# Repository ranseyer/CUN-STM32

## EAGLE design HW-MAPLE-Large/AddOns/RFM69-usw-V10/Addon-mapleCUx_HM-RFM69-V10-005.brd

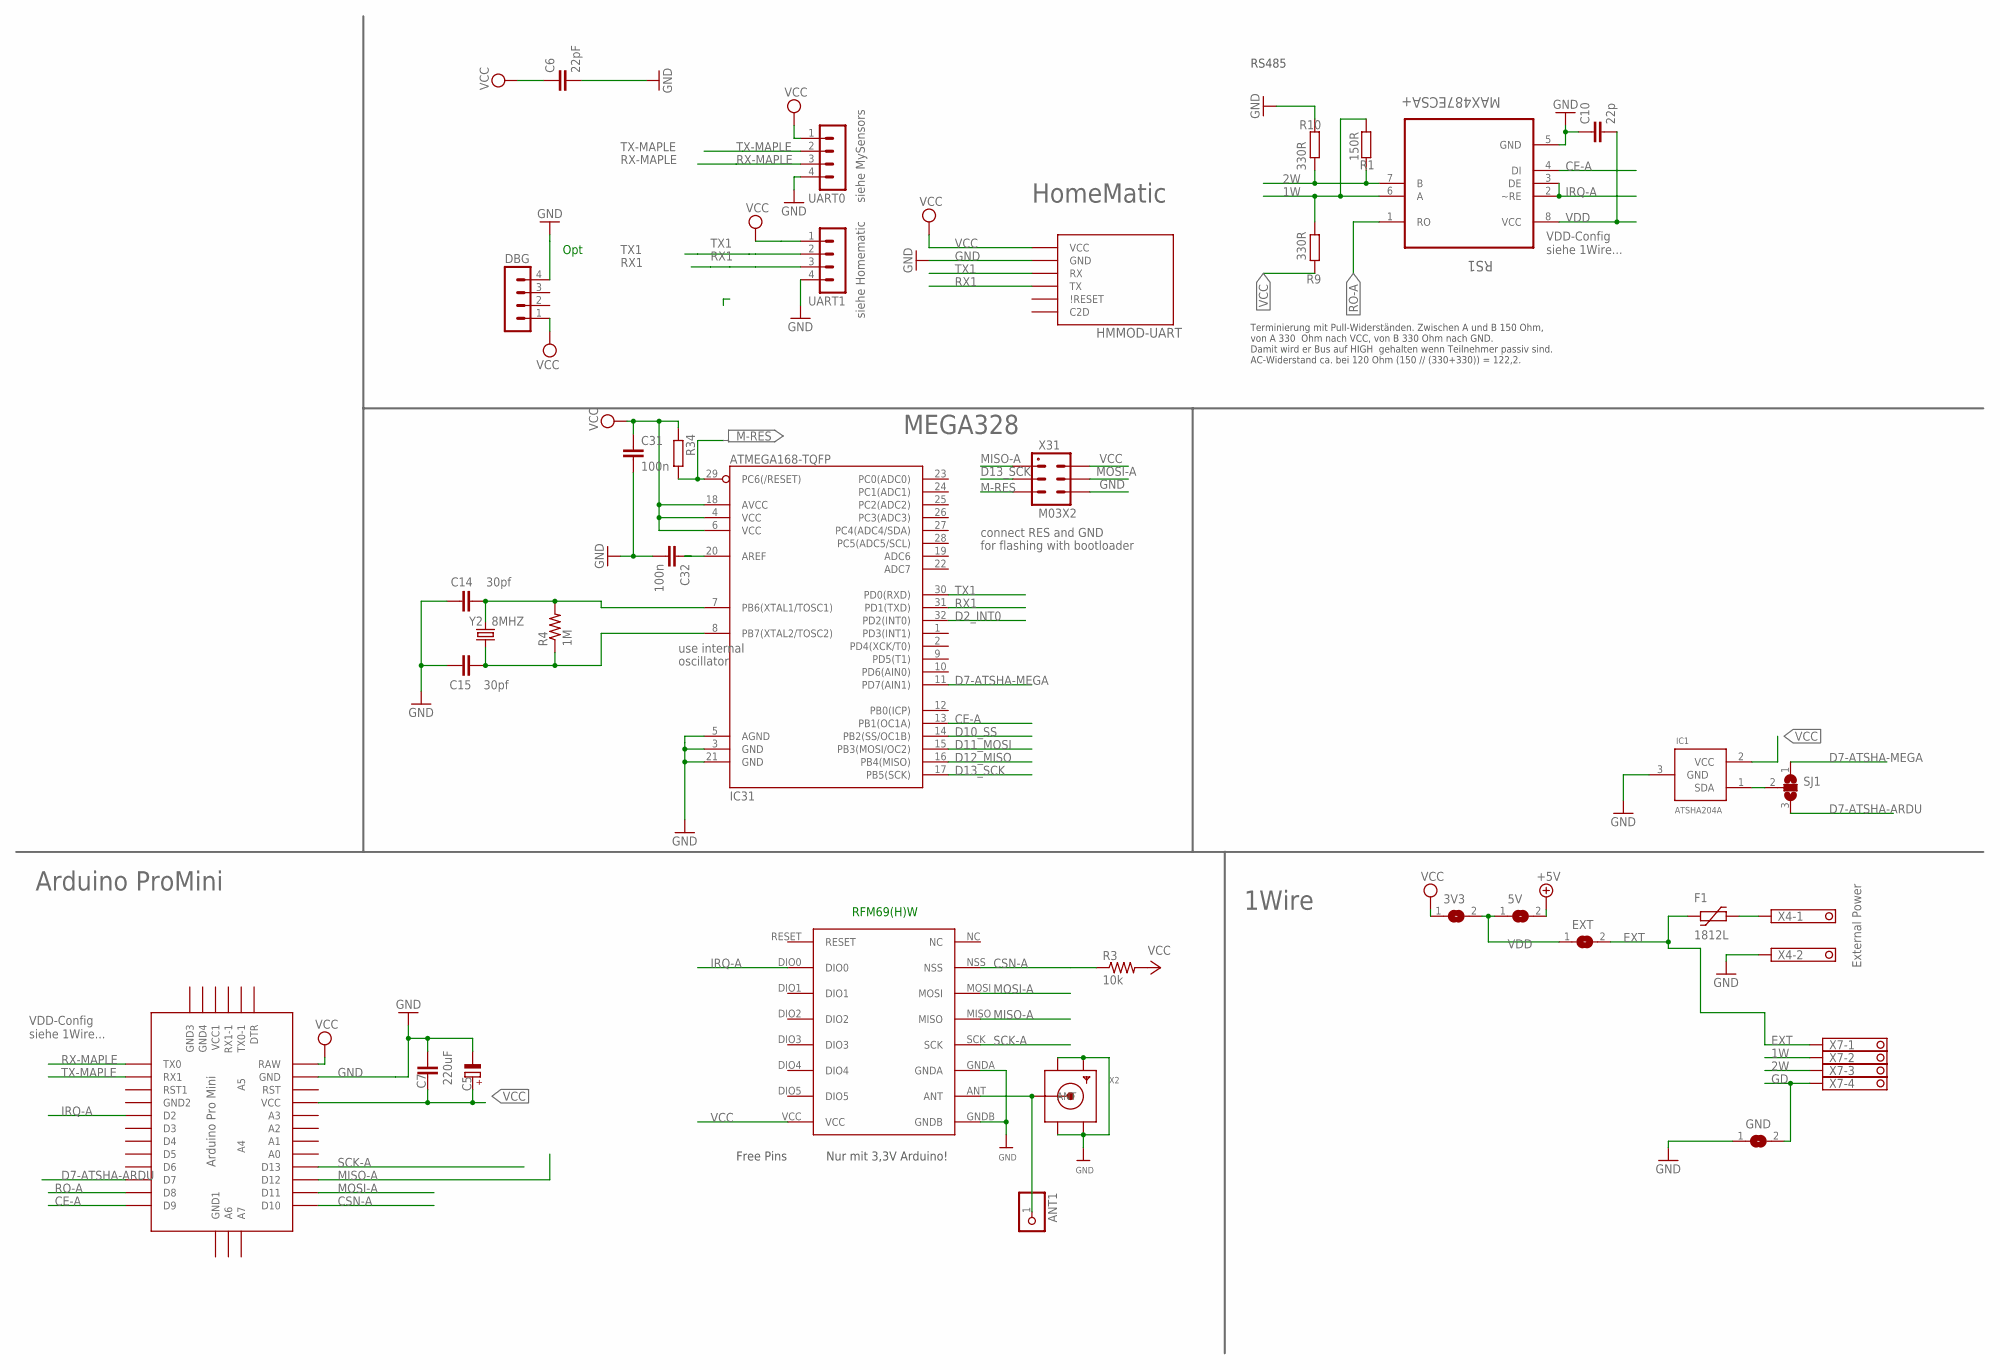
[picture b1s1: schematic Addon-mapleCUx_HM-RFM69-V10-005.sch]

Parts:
3V3, 5V: SJ
ANT1: PINHD-1X1; 1X01
C5: 220uF; E5-8,5
C6: 22pF; C0805
C7: C-EUC1812; C1812
C10: 22p; C0805
C14, C15: 30pf; 0805
C31, C32: 100n; C0805
DBG: MA04-1
EXT: SJ
F1: 1812L
GND: SJ
HMMOD-UART: HM-MOD-UARTDIL; HM-MOD-UART-DIL
IC1: ATSHA204A; SOT23
IC31: ATMEGA168-TQFP; TQFP32-08
R1: 150R; R0805
R3: 10k; 0805
R4: 1M; 0805
R9, R10: 330R; R0805
R34: R-EU_R0805; R0805
RFM69W: RFM69HW; RFM
RS1: MAX487ECSA+; SOIC127P600X175-8N
SJ1: SJ2W; SJ_2
U$2: ABK-PRO-MINI
UART0, UART1: MA04-1
X2: SMACONNECTOR_EDGE; SMA_EDGELAUNCH
X4: 1751248
X7: 1751264
X31: M03X2; 2X03-1.27MM_SMD
Y2: 8MHZ; CRYSTAL-TXC-7A

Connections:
1W: R1.1, R9.2, RS1.6 (A), X7.2
2W: R1.2, R10.1, RS1.7 (B), X7.3
+5V: 5V.2
CE-A: IC31.13 (PB1(OC1A)), RS1.4 (DI), U$2.D9
CSN-A: R3.1, RFM69W.NSS, U$2.D10
D2_INT0: IC31.32 (PD2(INT0))
D7-ATSHA-ARDU: SJ1.3, U$2.D7
D7-ATSHA-MEGA: IC31.11 (PD7(AIN1)), SJ1.1
D10_SS: IC31.14 (PB2(SS/OC1B))
D11_MOSI: IC31.15 (PB3(MOSI/OC2))
D12_MISO: IC31.16 (PB4(MISO))
D13_SCK: IC31.17 (PB5(SCK)), X31.P$3 (3)
EXT: EXT.2, F1.P$1 (1), X7.1
GD: GND.2, X7.4
GND: C5.-, C6.2, C7.1, C10.1, C14.1, C15.1, C31.2, C32.2, DBG.4, GND.1, HMMOD-UART.2 (GND), IC1.3 (GND), IC31.3 (GND), IC31.5 (AGND), IC31.21 (GND), R10.2, RFM69W.GNDA, RFM69W.GNDB, RS1.5 (GND), U$2.GND, UART0.4, UART1.4, X2.GND@1 (GND4), X2.GND@2 (GND3), X2.GND@3 (GND2), X2.GND@4 (GND1), X4.2, X31.P$6 (6)
IRQ-A: RFM69W.DIO0, RS1.2 (~RE), RS1.3 (DE), U$2.D2
M-RES: IC31.29 (PC6(/RESET)), R34.2, X31.P$5 (5)
MISO-A: RFM69W.MISO, U$2.D12, X31.P$1 (1)
MOSI-A: RFM69W.MOSI, U$2.D11, X31.P$4 (4)
unnamed: ANT1.1, RFM69W.ANT, X2.P (ANT)
unnamed: C14.2, IC31.7 (PB6(XTAL1/TOSC1)), R4.2, Y2.P$2 (2)
unnamed: IC1.1 (SDA), SJ1.2
unnamed: C32.1, IC31.20 (AREF)
unnamed: C15.2, IC31.8 (PB7(XTAL2/TOSC2)), R4.1, Y2.P$1 (1)
unnamed: F1.P$2 (2), X4.1
RO-A: RS1.1 (RO), U$2.D8
RX1: HMMOD-UART.5 (TX), IC31.31 (PD1(TXD)), UART1.3
RX-MAPLE: U$2.TX0, UART0.3
SCK-A: RFM69W.SCK, U$2.D13
TX1: HMMOD-UART.6 (RX), IC31.30 (PD0(RXD)), UART1.2
TX-MAPLE: U$2.RX1, UART0.2
VCC: 3V3.1, C5.+, C6.1, C7.2, C31.1, DBG.1, HMMOD-UART.1 (VCC), IC1.2 (VCC), IC31.4 (VCC), IC31.6 (VCC), IC31.18 (AVCC), R3.2, R9.1, R34.1, RFM69W.VCC, U$2.RAW, U$2.VCC, UART0.1, UART1.1, X31.P$2 (2)
VDD: 3V3.2, 5V.1, C10.2, EXT.1, RS1.8 (VCC)

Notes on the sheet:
Opt
siehe Homematic
siehe MySensors
HomeMatic
Arduino ProMini
MEGA328
VDD-Config siehe 1Wire...
use internal
oscillator
connect RES and GND
for flashing with bootloader
RS485
Terminierung mit Pull-Widerständen. Zwischen A und B 150 Ohm, von A 330 Ohm nach VCC, von B 330 Ohm nach GND. Damit wird er Bus auf HIGH gehalten wenn Teilnehmer passiv sind. AC-Widerstand ca. bei 120 Ohm (150 // (330+330)) = 122,2.
1Wire
External Power
Free Pins
RFM69(H)W
Nur mit 3,3V Arduino!

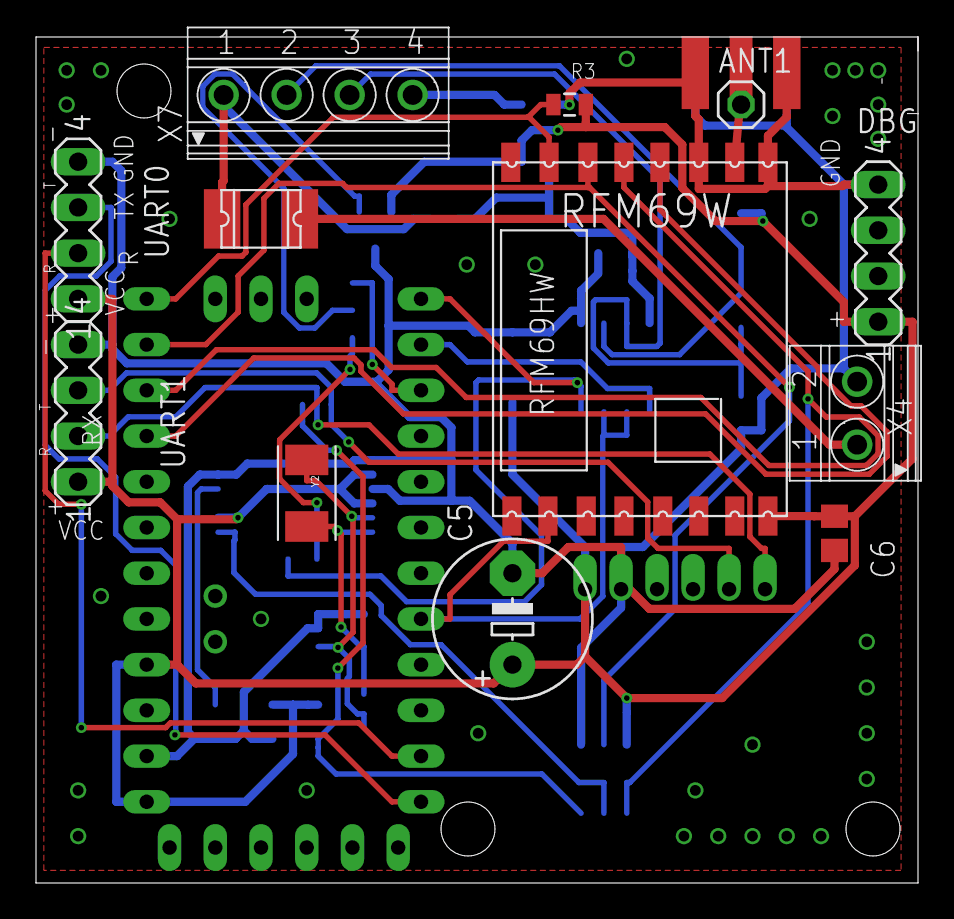
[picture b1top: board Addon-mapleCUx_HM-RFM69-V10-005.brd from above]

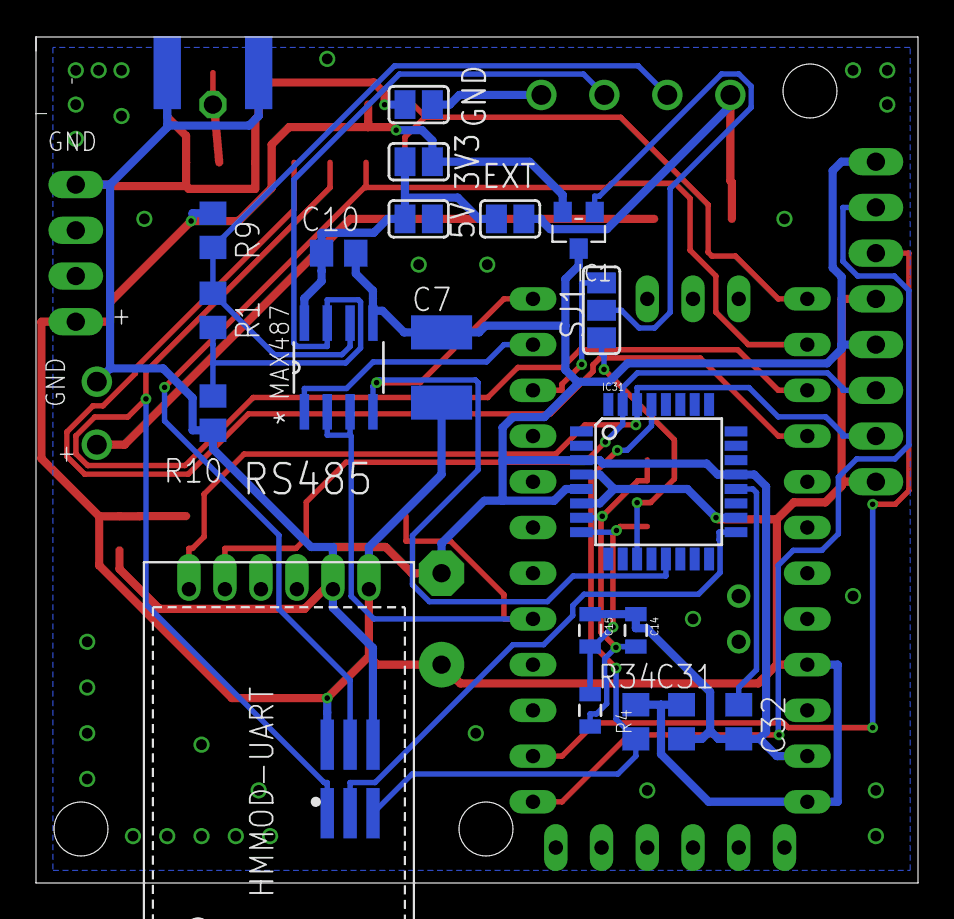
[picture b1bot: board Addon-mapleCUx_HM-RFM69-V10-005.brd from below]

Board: 2 copper layers, 49.0 x 47.0 mm, 35 parts (21 on the bottom side), 28 nets.

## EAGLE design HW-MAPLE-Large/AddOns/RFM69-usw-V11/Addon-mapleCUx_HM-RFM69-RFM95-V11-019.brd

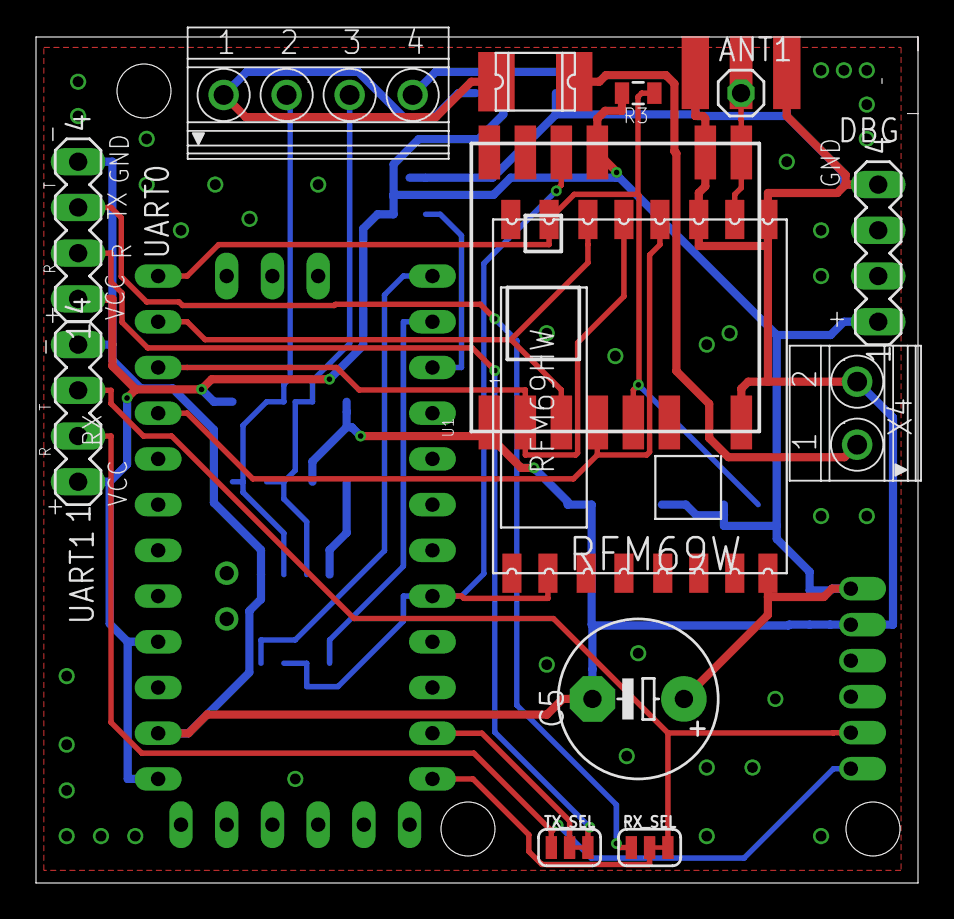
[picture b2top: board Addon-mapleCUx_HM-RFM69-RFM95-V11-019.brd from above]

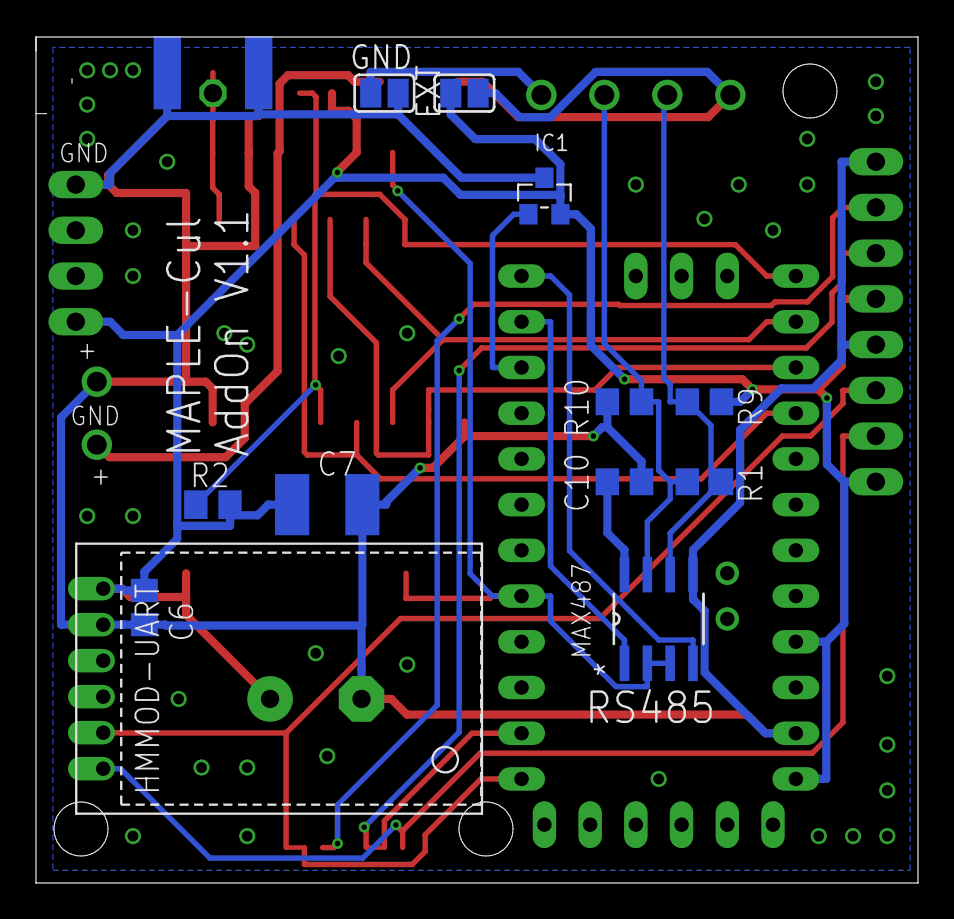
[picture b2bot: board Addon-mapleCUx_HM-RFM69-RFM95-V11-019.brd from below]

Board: 2 copper layers, 49.0 x 47.0 mm, 27 parts (12 on the bottom side), 23 nets.

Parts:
ANT1: 1X01
C5: 220uF; E5-8,5
C6: 22pF; C0805
C7: C1812
C10: 22p; C0805
DBG: MA04-1
EXT: SJ
F1: 1812L
GND: SJ
HMMOD-UART: HM-MOD-UARTDIL; HM-MOD-UART-DIL
IC1: ATSHA204A; SOT23
R1: 150R; R0805
R2: 10k; M0805
R3: 10k; 0805
R9, R10: 330R; R0805
RFM69W: RFM69HW; RFM
RS1: MAX487ECSA+; SOIC127P600X175-8N
RX_SEL: JUMPER-SMT_3_1-NC_TRACE_SILK; SMT-JUMPER_3_1-NC_TRACE_SILK
TX_SEL: JUMPER-SMT_3_1-NC_TRACE_SILK; SMT-JUMPER_3_1-NC_TRACE_SILK
U1: RFM69HCW; RFM69HCW-XXXS2
U$2: ABK-PRO-MINI
UART0, UART1: MA04-1
X2: SMA_EDGELAUNCH
X4: 1751248
X7: 1751264

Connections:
1W: R1.1, R9.2, RS1.6, X7.2
2W: R1.2, R10.1, RS1.7, X7.3
ANT: ANT1.1, RFM69W.ANT, U1.ANT, X2.P
CE-A: RS1.4, U$2.D9
CSN-A: R2.1, R3.1, RFM69W.NSS, U1.NSS, U$2.D10
D7-ATSHA-ARDU: IC1.1, U$2.D7
EXT: EXT.2, F1.P$1, X7.1
GD: GND.2, X7.4
GND: C5.-, C6.2, C7.1, C10.1, DBG.4, GND.1, HMMOD-UART.2, IC1.3, R10.2, RFM69W.GNDA, RFM69W.GNDB, RS1.5, U1.GND_1, U1.GND_2, U1.GND_3, U$2.GND, UART0.4, UART1.4, X2.GND@1, X2.GND@2, X2.GND@3, X2.GND@4, X4.2
IRQ-A: RFM69W.DIO0, RS1.2, RS1.3, U1.DIO0, U$2.D2
MISO-A: RFM69W.MISO, U1.MISO, U$2.D12
MOSI-A: RFM69W.MOSI, U1.MOSI, U$2.D11
unnamed: F1.P$2, X4.1
RO-A: RS1.1, U$2.D8
RX: TX_SEL.2, U$2.RX1
RX0: RX_SEL.1, UART0.3
RX1: HMMOD-UART.5, RX_SEL.3, UART1.3
SCK-A: RFM69W.SCK, U1.SCK, U$2.D13
TX: RX_SEL.2, U$2.TX0
TX0: TX_SEL.3, UART0.2
TX1: HMMOD-UART.6, TX_SEL.1, UART1.2
VCC: C5.+, C6.1, C7.2, DBG.1, EXT.1, HMMOD-UART.1, IC1.2, R2.2, R3.2, R9.1, RFM69W.VCC, U1.3.3V, U$2.RAW, U$2.VCC, UART0.1, UART1.1
VDD: C10.2, RS1.8

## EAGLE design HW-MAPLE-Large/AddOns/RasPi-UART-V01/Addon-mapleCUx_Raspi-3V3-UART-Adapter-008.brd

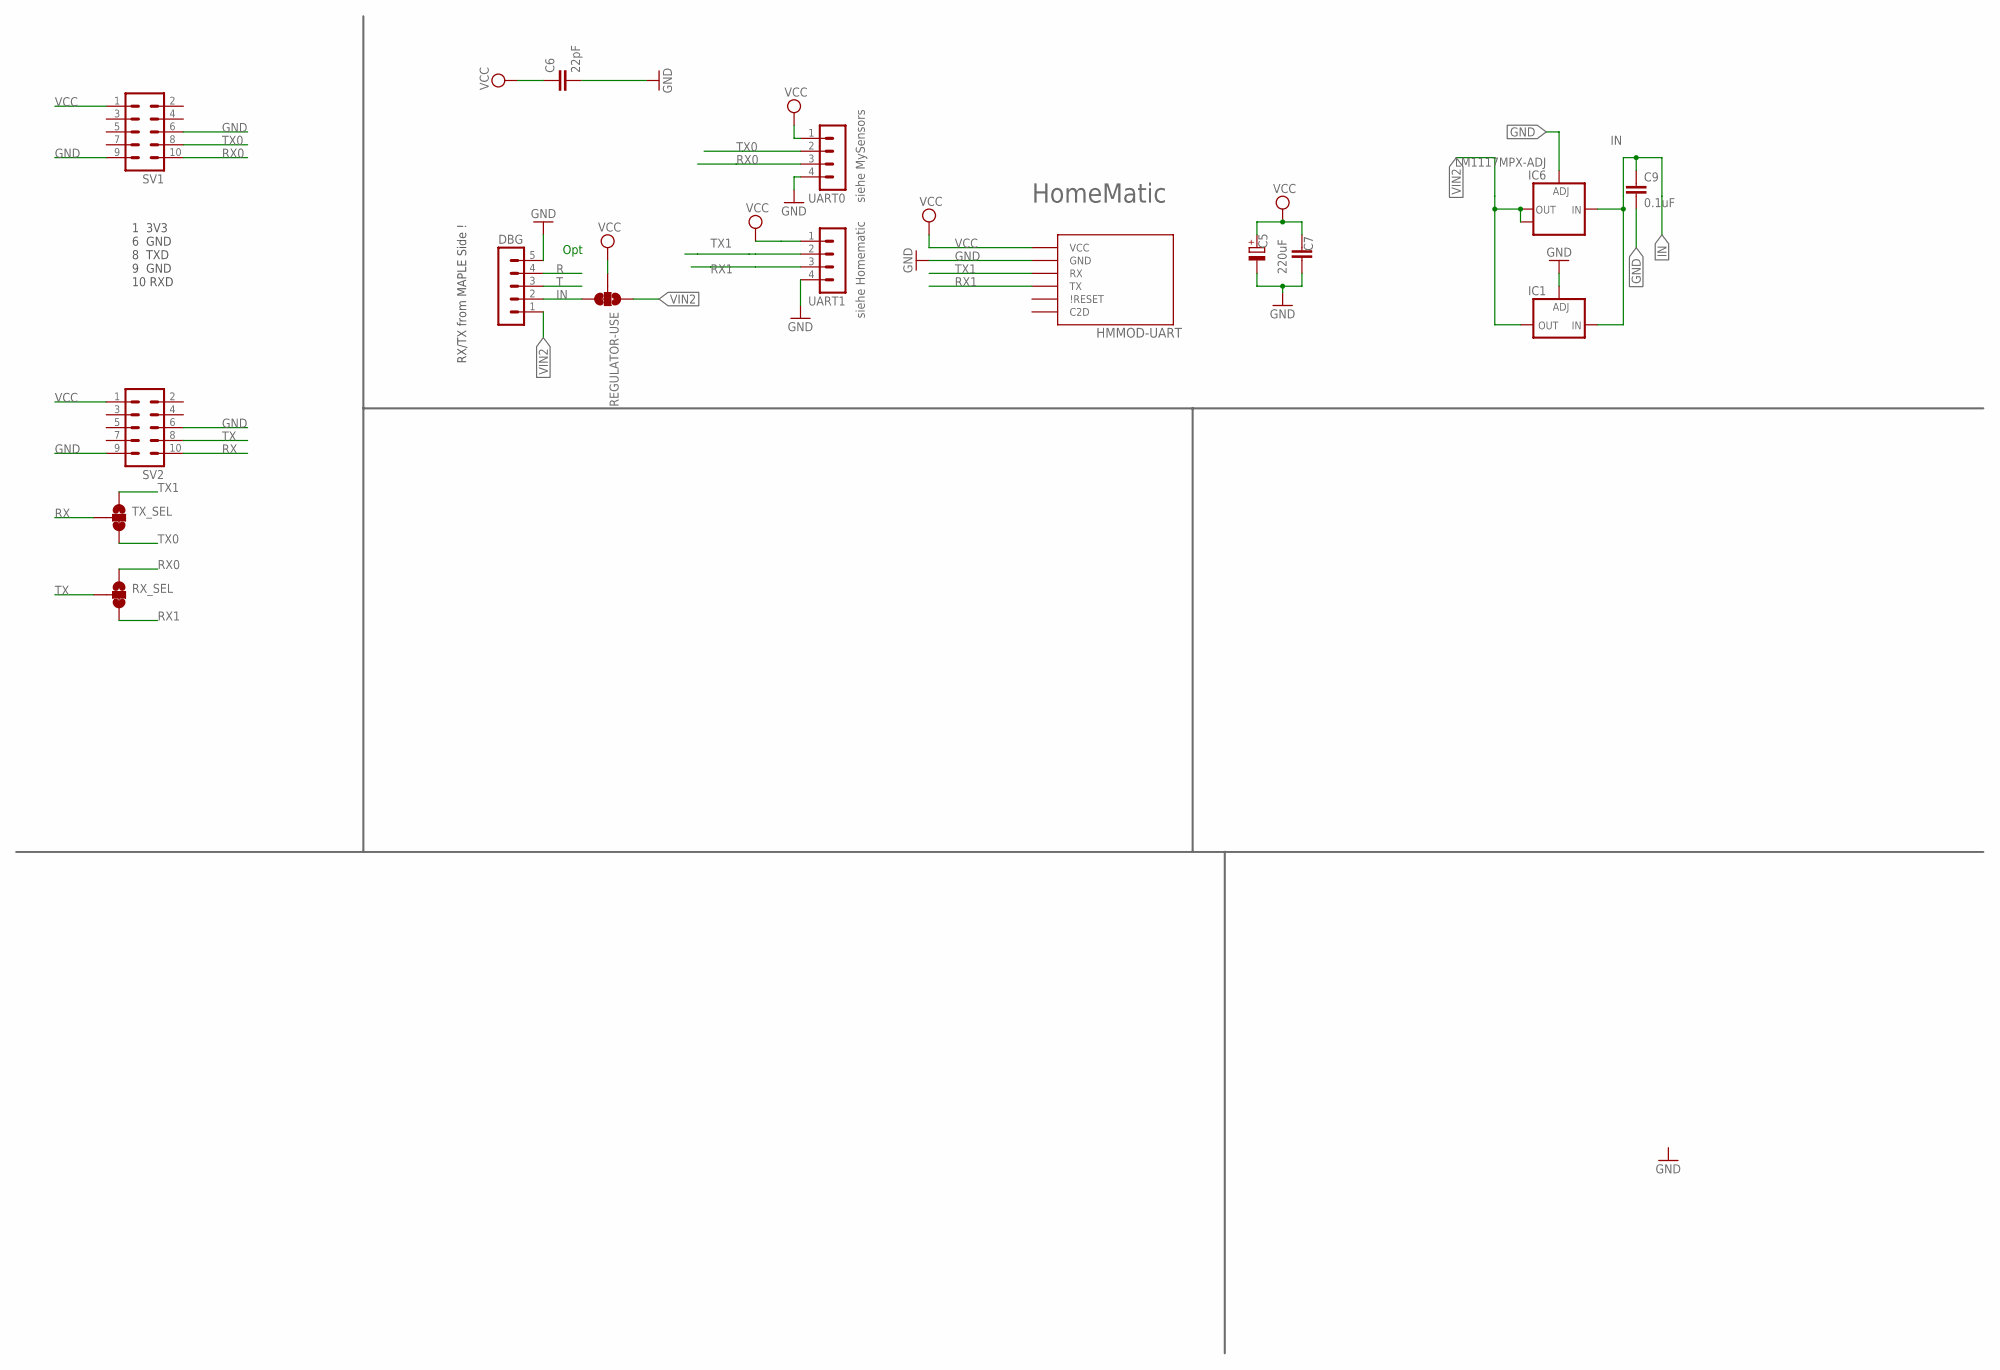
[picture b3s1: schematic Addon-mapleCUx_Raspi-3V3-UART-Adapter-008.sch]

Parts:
C5: 220uF; E5-8,5
C6: 22pF; C0805
C7: C-EUC1812; C1812
C9: 0.1uF; C1206
DBG: MA05-1
HMMOD-UART: HM-MOD-UARTDIL; HM-MOD-UART-DIL
IC1: LD117ADT50TR; DPACK
IC6: LM1117MPX-ADJ; SOT223
REGULATOR-USE: JUMPER-SMT_3_1-NC_TRACE_SILK; SMT-JUMPER_3_1-NC_TRACE_SILK
RX_SEL: JUMPER-SMT_3_1-NC_TRACE_SILK; SMT-JUMPER_3_1-NC_TRACE_SILK
SV1, SV2: MA05-2
TX_SEL: JUMPER-SMT_3_1-NC_TRACE_SILK; SMT-JUMPER_3_1-NC_TRACE_SILK
UART0, UART1: MA04-1

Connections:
GND: C5.-, C6.2, C7.1, C9.2, DBG.5, HMMOD-UART.2 (GND), IC1.1 (ADJ), IC6.1 (ADJ), SV1.6, SV1.9, SV2.6, SV2.9, UART0.4, UART1.4
IN: C9.1, DBG.2, IC1.3 (IN), IC6.3 (IN), REGULATOR-USE.3
R: DBG.4
RX: SV2.10, TX_SEL.2
RX0: RX_SEL.1, SV1.10, UART0.3
RX1: HMMOD-UART.5 (TX), RX_SEL.3, UART1.3
T: DBG.3
TX: RX_SEL.2, SV2.8
TX0: SV1.8, TX_SEL.3, UART0.2
TX1: HMMOD-UART.6 (RX), TX_SEL.1, UART1.2
VCC: C5.+, C6.1, C7.2, HMMOD-UART.1 (VCC), REGULATOR-USE.2, SV1.1, SV2.1, UART0.1, UART1.1
VIN2: DBG.1, IC1.4 (OUT), IC6.2 (OUT), IC6.TAB (OUT1), REGULATOR-USE.1

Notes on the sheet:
Opt
siehe Homematic
siehe MySensors
HomeMatic
1 3V3 6 GND 8 TXD 9 GND 10 RXD
RX/TX from MAPLE Side !

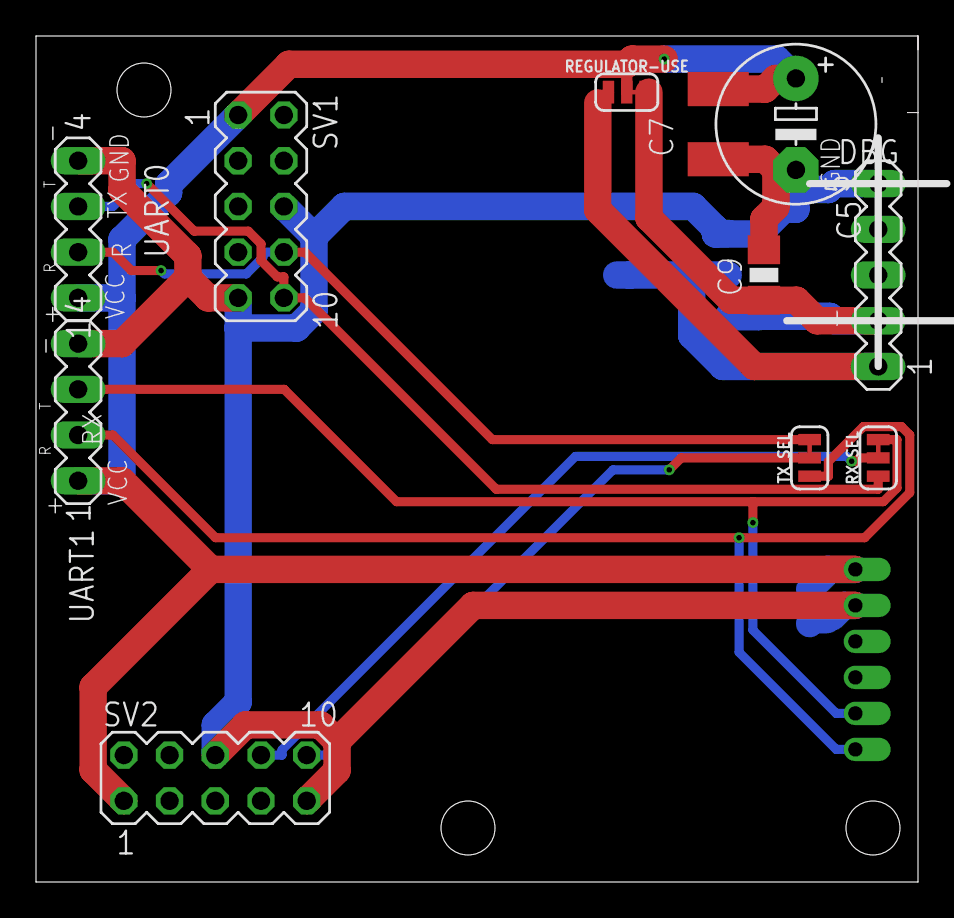
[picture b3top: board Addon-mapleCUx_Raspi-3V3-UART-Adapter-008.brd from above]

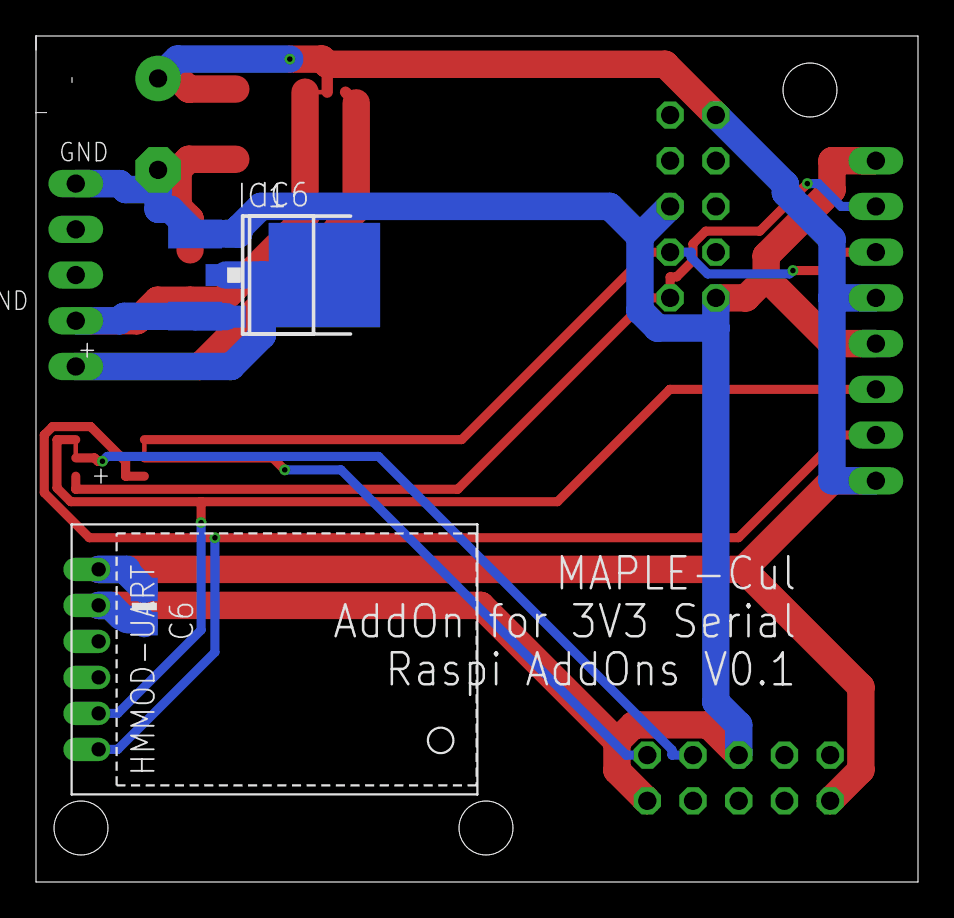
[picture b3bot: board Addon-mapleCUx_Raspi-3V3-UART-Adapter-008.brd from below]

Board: 2 copper layers, 49.0 x 47.0 mm, 15 parts (4 on the bottom side), 10 nets.

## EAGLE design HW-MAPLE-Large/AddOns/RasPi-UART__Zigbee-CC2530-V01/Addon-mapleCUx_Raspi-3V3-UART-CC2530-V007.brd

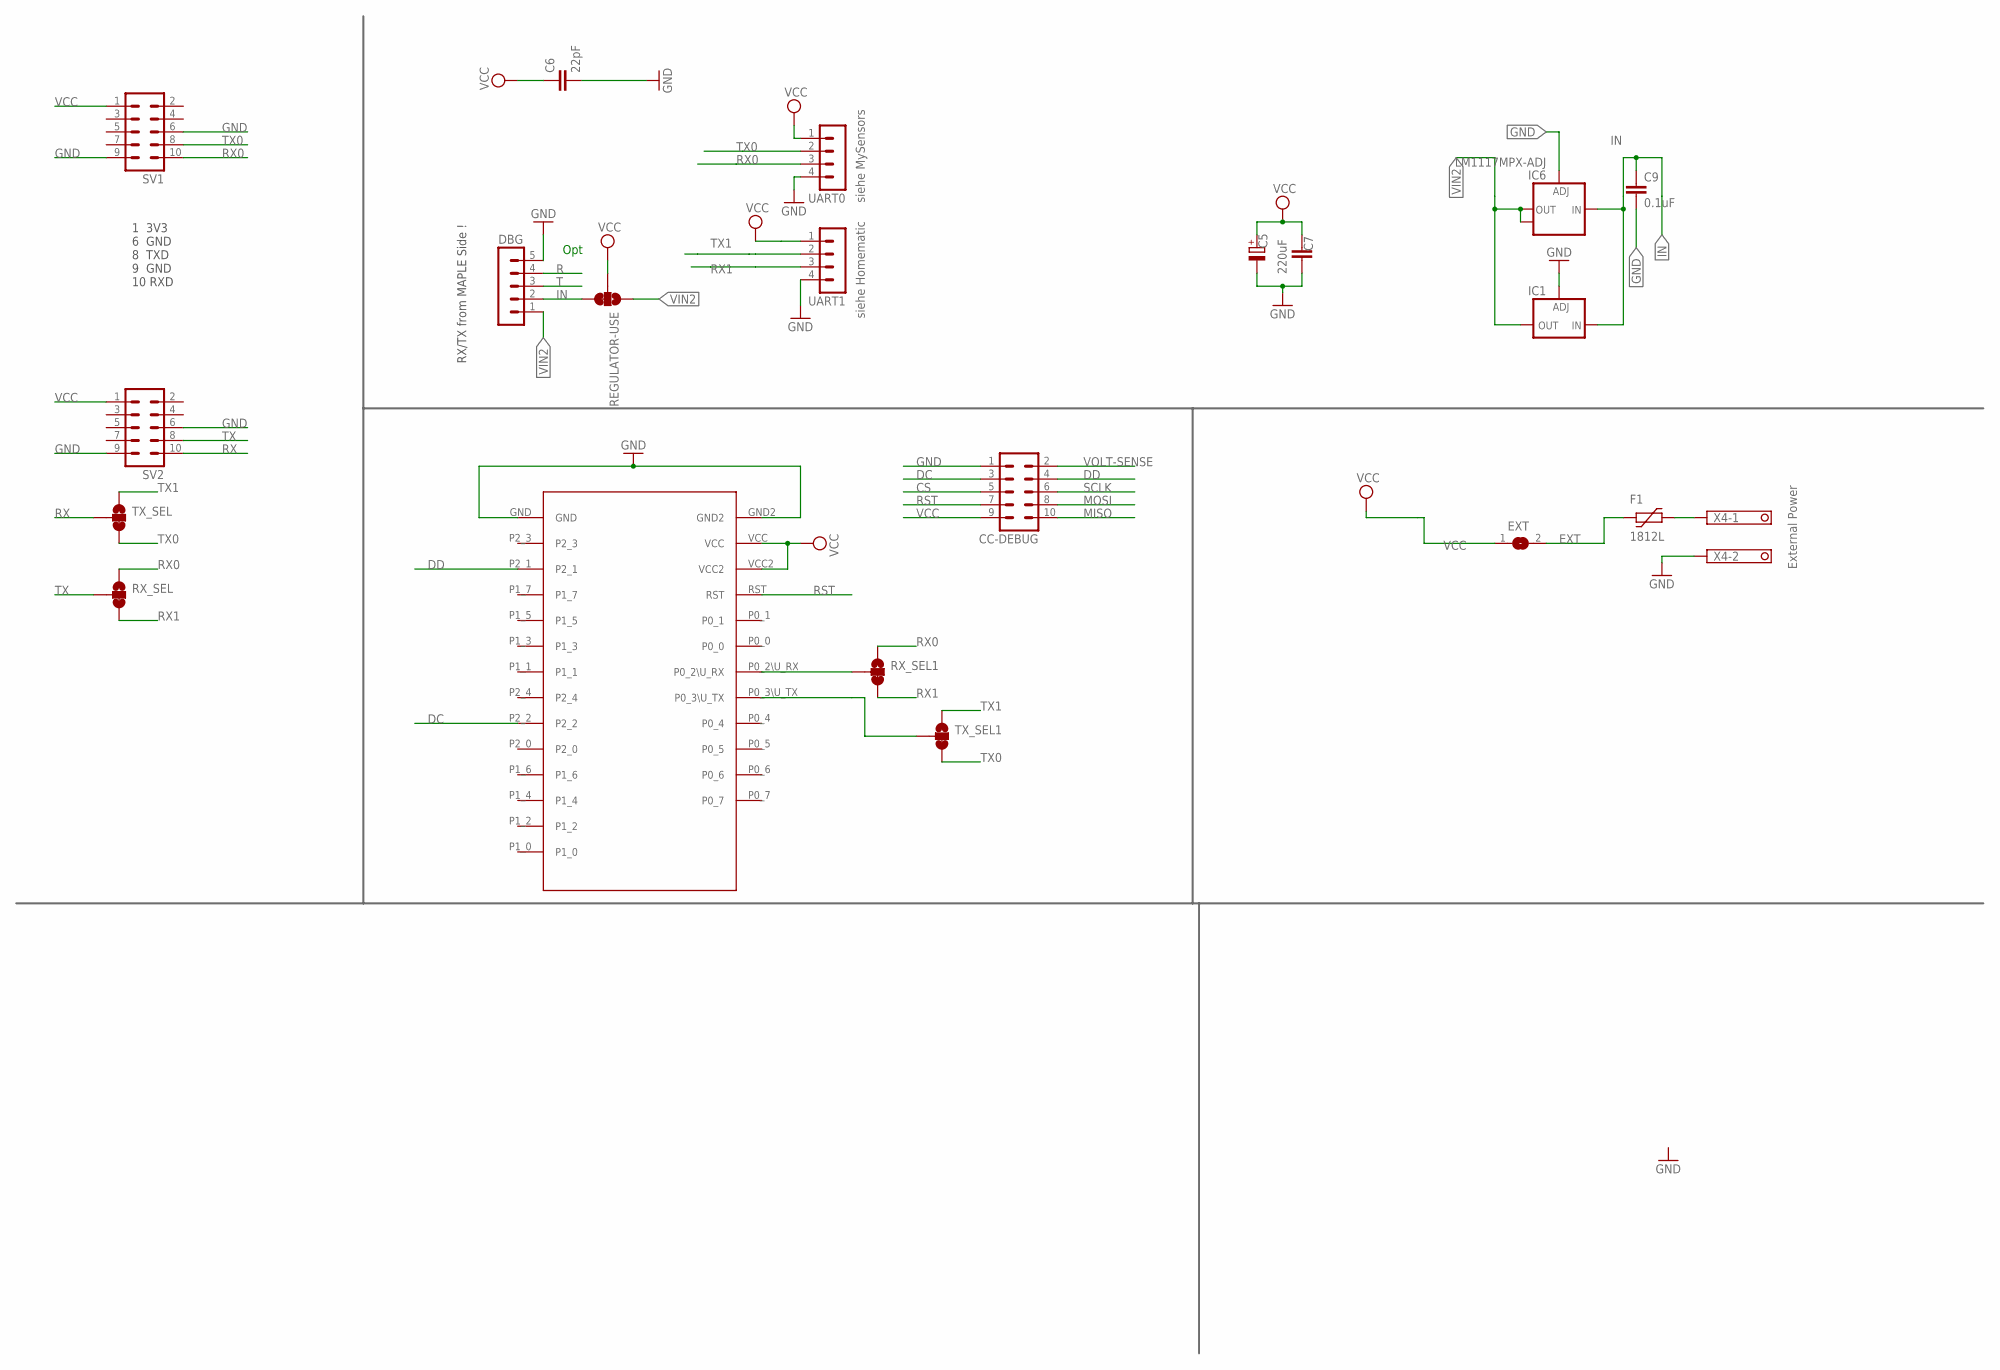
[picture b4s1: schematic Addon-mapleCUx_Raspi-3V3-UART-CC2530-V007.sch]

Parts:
C5: 220uF; E5-8,5
C6: 22pF; C0805
C7: C-EUC1812; C1812
C9: 0.1uF; C1206
CC-DEBUG: MA05-2
DBG: MA05-1
EXT: SJ
F1: 1812L
IC1: LD117ADT50TR; DPACK
IC6: LM1117MPX-ADJ; SOT223
REGULATOR-USE: JUMPER-SMT_3_1-NC_TRACE_SILK; SMT-JUMPER_3_1-NC_TRACE_SILK
RX_SEL, RX_SEL1: JUMPER-SMT_3_1-NC_TRACE_SILK; SMT-JUMPER_3_1-NC_TRACE_SILK
SV1, SV2: MA05-2
TX_SEL, TX_SEL1: JUMPER-SMT_3_1-NC_TRACE_SILK; SMT-JUMPER_3_1-NC_TRACE_SILK
U$3: CC2530_MODULE; CC2530_DIL
UART0, UART1: MA04-1
X4: 1751248

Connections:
CS: CC-DEBUG.5
DC: CC-DEBUG.3, U$3.P2_2
DD: CC-DEBUG.4, U$3.P2_1
EXT: EXT.2, F1.P$1 (1)
GND: C5.-, C6.2, C7.1, C9.2, CC-DEBUG.1, DBG.5, IC1.1 (ADJ), IC6.1 (ADJ), SV1.6, SV1.9, SV2.6, SV2.9, U$3.GND, U$3.GND2, UART0.4, UART1.4, X4.2
IN: C9.1, DBG.2, IC1.3 (IN), IC6.3 (IN), REGULATOR-USE.3
MISO: CC-DEBUG.10
MOSI: CC-DEBUG.8
unnamed: RX_SEL1.2, U$3.P0_2\U_RX
unnamed: TX_SEL1.2, U$3.P0_3\U_TX
unnamed: F1.P$2 (2), X4.1
R: DBG.4
RST: CC-DEBUG.7, U$3.RST
RX: SV2.10, TX_SEL.2
RX0: RX_SEL.1, RX_SEL1.1, SV1.10, UART0.3
RX1: RX_SEL.3, RX_SEL1.3, UART1.3
SCLK: CC-DEBUG.6
T: DBG.3
TX: RX_SEL.2, SV2.8
TX0: SV1.8, TX_SEL.3, TX_SEL1.3, UART0.2
TX1: TX_SEL.1, TX_SEL1.1, UART1.2
VCC: C5.+, C6.1, C7.2, CC-DEBUG.9, EXT.1, REGULATOR-USE.2, SV1.1, SV2.1, U$3.VCC, U$3.VCC2, UART0.1, UART1.1
VIN2: DBG.1, IC1.4 (OUT), IC6.2 (OUT), IC6.TAB (OUT1), REGULATOR-USE.1
VOLT-SENSE: CC-DEBUG.2

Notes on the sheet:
Opt
siehe Homematic
siehe MySensors
1 3V3 6 GND 8 TXD 9 GND 10 RXD
RX/TX from MAPLE Side !
External Power

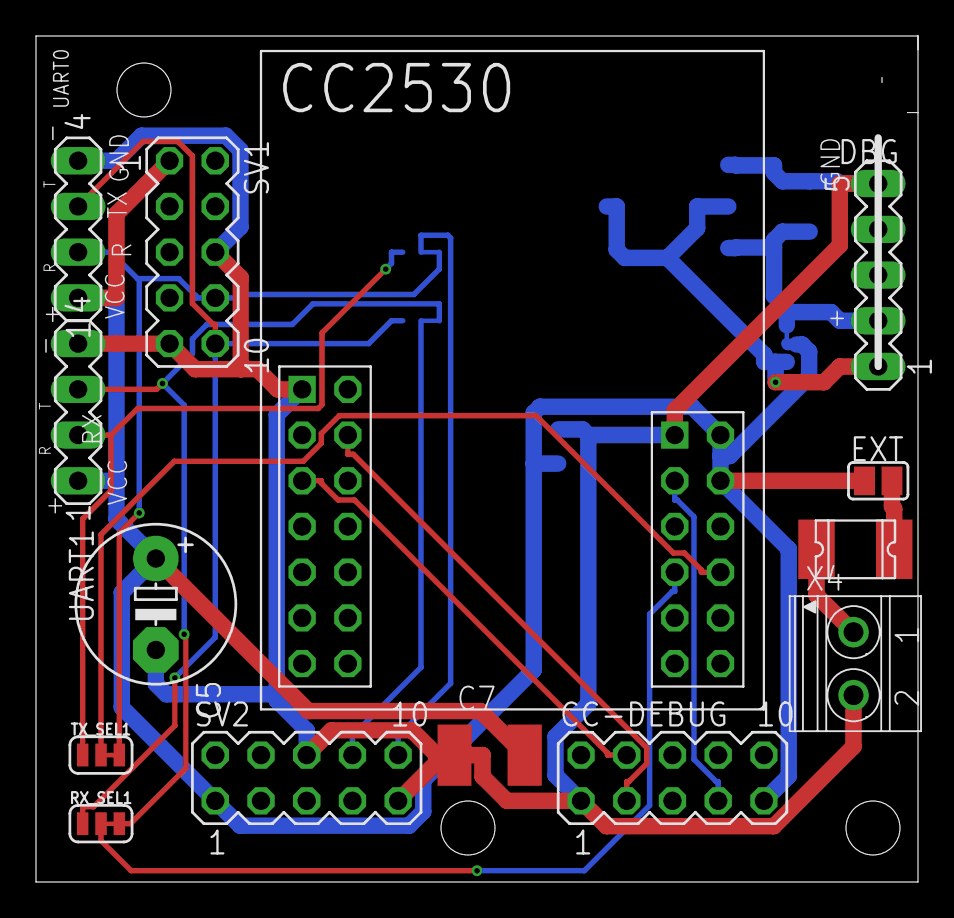
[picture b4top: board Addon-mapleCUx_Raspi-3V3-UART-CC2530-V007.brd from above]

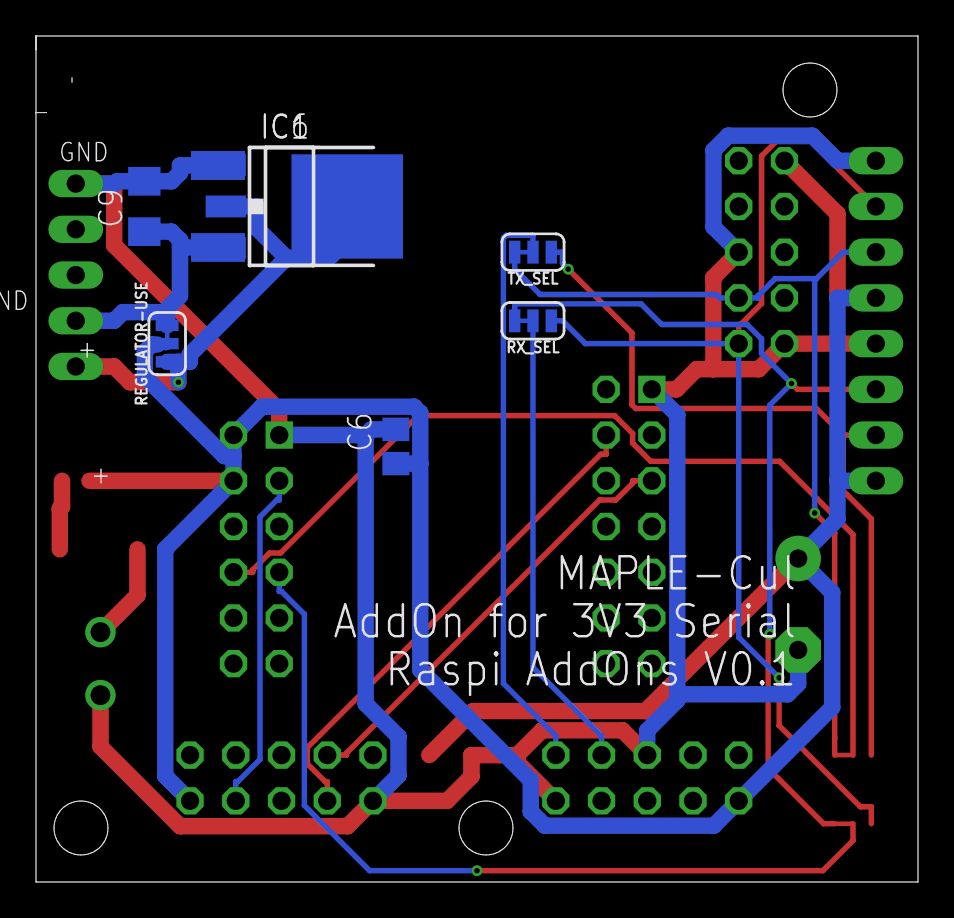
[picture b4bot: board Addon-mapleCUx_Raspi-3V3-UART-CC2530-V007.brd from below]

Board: 2 copper layers, 49.0 x 47.0 mm, 21 parts (7 on the bottom side), 17 nets.

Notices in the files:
parts and their libraries:
SparkFun-FreqCtrl: Licensing: Creative Commons ShareAlike 4.0 International - https://creativecommons.org/licenses/by-sa/4.0
microbuilder: This work is placed in the public domain, and may be freely used for commercial and non-commercial work with the following conditions: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
